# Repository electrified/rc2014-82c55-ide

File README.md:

# 82c55 based IDE interface for the RC2014 computer

## The board
This is a 82c55 based IDE interface for the RC2014 Z80 8-bit computer. IDE uses a 16 bit data bus, so a parallel interface IC is needed to connect one to an 8 bit computer.
This adapter uses the same pin mapping as the ECB Disk IO v3 and the design is heavily based on that. (https://www.retrobrewcomputers.org/lib/exe/fetch.php?media=boards:ecb:diskio-v3:ecb_diskio_v3_-_schematics_-_color_1.0.pdf)

## What can you use this for?

* Connecting an IDE hard drive to your RC2014 and using it in RomWBW, CP/M-IDE or in C programs built with z88dk.

## Features

* 40 pin IDE for normal 3.5" hard drives
* 44 pin IDE header for 2.5" laptop hard drives
* Pins for supplying external 5v for the laptop HD if necessary
* IO port selectable via DIP switch

## Getting started with RomWBW
Wayne Warthen has incorporated support for the RC2014 into [mainline RomWBW](https://github.com/wwarthen/RomWBW). Using this is preferred to Scott Baker's fork as there have been various improvements since Scott forked off. Support for the IDE adapter can be enabled by setting the following in your configuration and rebuilding:

```
PPIDEENABLE     .EQU    TRUE
```

Read the RomWBW readme (`Source/ReadMe.txt`) if you are unfamiliar with the configuration and build process.

The other settings have already been set to the appropriate values in `Source/HBIOS/cfg_rc.asm`, so all is required is to enable PPIDE.

The board I/O address should be set to 0x20; set the A5 switch "on" and all the others off.

## Getting started with z88dk
Support has only recently landed so you'll need a very recent pull of z88dk.
The 82c55 driver, IDE layer and DiskIO are only present within z88dk's RC2014 newlib target. (Not the classic library). 

Phillip Stevens has packaged ChaN's FatFS as a z88dk library, this can be used with above z88dk IDE driver to write programs that can access FAT filesystems.

See https://github.com/feilipu/z88dk-libraries/tree/master/ff and the programs in the example directory.

## CP/M - IDE
Phillip Stevens has made a CP/M version where the CP/M disk images can reside on a FAT filesystem. This requires only a minimal RC2014 setup. See [the GitHub repository](https://github.com/RC2014Z80/RC2014/tree/master/ROMs/CPM-IDE) and [Google groups thread](https://groups.google.com/forum/#!topic/rc2014-z80/V07eugtGFZo) for more details.

## Jumpers and switches
Pin 1 is identified by having square pad.

### SW1
IO address of the board. For operation at 0x20 as RomWBW expects, set the switch marked A5 / 20 to on and all the others to off.

### JP1 - JP4
Described on the back of the board. Some of the pins in the 82c55 C port have a special purpose if you are using the board in mode 2, for something other than being an IDE adapter. Usually the defaults of pins 2-3 are correct.

### JP5
Use external power from J1. Rev 2 of the board only has 2 pins, jumper for bus power.

pins|description
----|------------
1-2 | Bus power
2-3 | External power

## Outputs

* J2 - 40 pin IDE
* J3 - 44 pin IDE

## Bill Of Materials

Reference| Value|Rapid part no|RS part no|Digi-key part no|
---------|------|-------------|----------|----------------|
P1|1x39 right angled pin header|||732-5350-ND|
U1|CS82C55AZ (PLCC version)||921-5567|CS82C55AZ-ND|
U1|PLCC44 socket|22-0350||AE10057-ND|
U3|74HCT04 (DIP)|||296-1605-5-ND|
J2|2x20 shrouded right angled pin header|19-0047||732-5401-ND|
D1|LED of your choosing ;)|||160-1130-ND|
R1|270R through hole resistor (or value suitable for chosen LED)|||CF14JT270RCT-ND|
U2|74HCT688 (DIP)|||296-2131-5-ND|
RN1|10K commoned SIP resistor array (7 resistors, 8 pin)|63-0125||4608X-1-103LF-ND|
C1|0.1uF ceramic capacitor|||BC2665CT-ND|
C2|0.1uF ceramic capacitor|||BC2665CT-ND|
C3|0.1uF ceramic capacitor|||BC2665CT-ND|
J3|2.5" IDE connector 2x22 Shrouded 2mm pitch connector|||WM18567-ND|
SW1|6 switch DIP switch|80-0338||CT2066-ND|
J5|1x02 pin header straight, 2.54mm pitch|||732-5315-ND|
J1|1x02 pin header straight, 2.54mm pitch|||732-5315-ND|
JP1|1x03 pin header straight, 2.54mm pitch|||732-5316-ND|
JP2|1x03 pin header straight, 2.54mm pitch|||732-5316-ND|
JP3|1x03 pin header straight, 2.54mm pitch|||732-5316-ND|
JP4|1x03 pin header straight, 2.54mm pitch|||732-5316-ND|
R3|10K through hole resistor|||CF14JT10K0CT-ND|
R4|10K through hole resistor|||CF14JT10K0CT-ND|
R2|10K through hole resistor|||CF14JT10K0CT-ND|
||Jumpers|||952-2882-ND|

## Construction tips
* Pin 20 of both the 40 pin and 44 pin IDE connector is usually missing as a "key" and is blocked off on many cables. It's best to remove pin 20 from both connectors before soldering them.
* If you're using a 2.5" and powering it from the bus, ensure you have a sufficient power supply. As an example, my 2.5" Seagate Momentum drive is specced to pull up to 2.5A on startup
* If you are using the board as an IDE controller, keep the JP1-4 in their default position of 2-3
* The cutout on the boxed IDE connectors should be towards the RC2014 bus connector in the case of the 44 pin connector, and facing the user in the case of the 40 pin connector.

## Compatibility
The IDE board will not work if the Digital IO v1.0 board is present in your RC2014. This is due to the IO board having very loose addressing - it responds on any IO address below 128 ending with binary 00, 01 or 10. This results in it conflicitng with the IDE adapter.

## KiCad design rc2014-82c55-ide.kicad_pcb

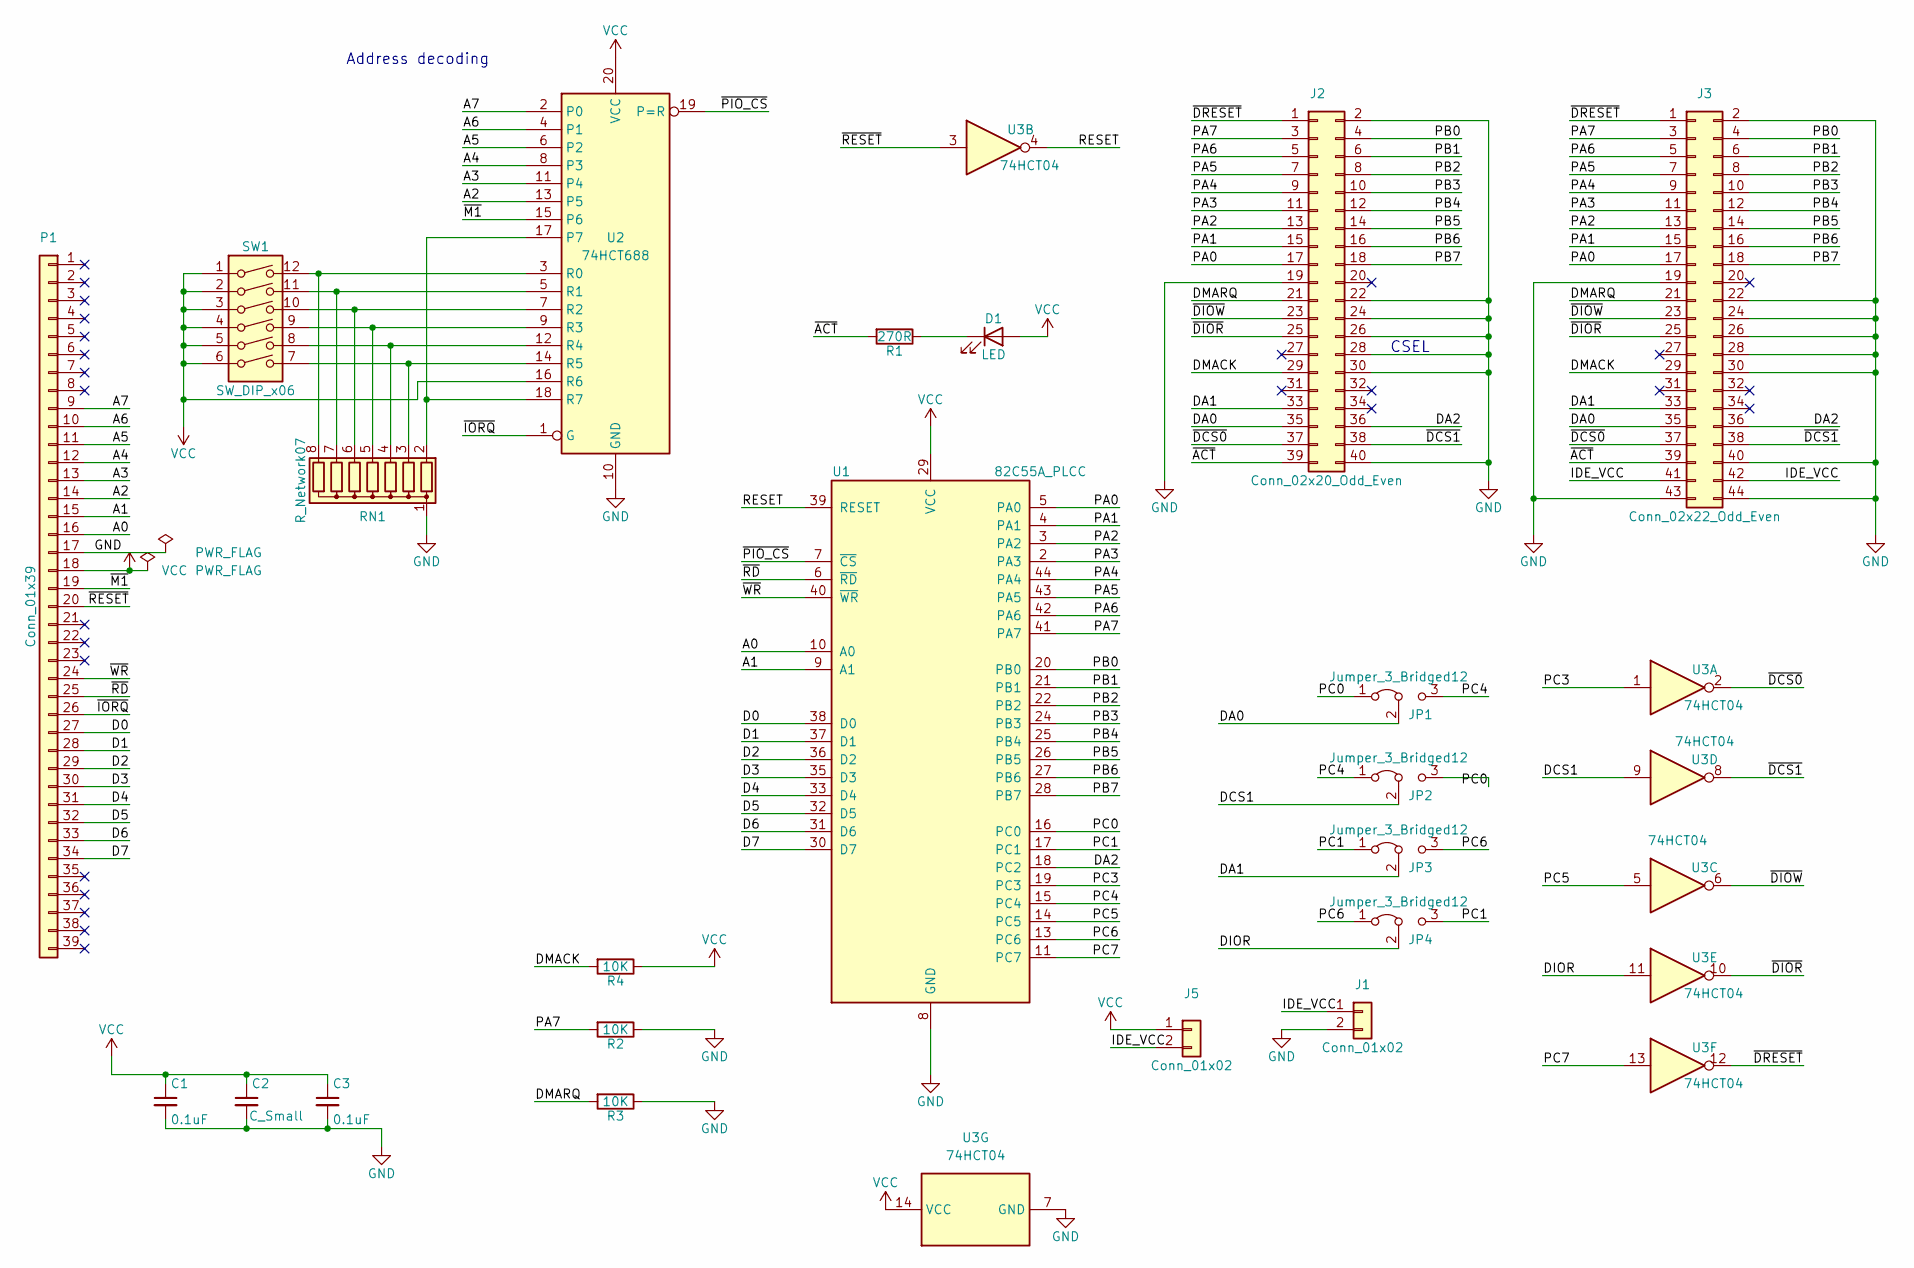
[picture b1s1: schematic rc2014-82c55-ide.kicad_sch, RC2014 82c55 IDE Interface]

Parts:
C1, C3: 0.1uF; C_Disc_D3.0mm_W2.0mm_P2.50mm
C2: C_Small; C_Disc_D3.0mm_W2.0mm_P2.50mm
D1: LED; LED_D3.0mm
J1, J5: Conn_01x02; PinHeader_1x02_P2.54mm_Vertical
J2: Conn_02x20_Odd_Even; PinHeader_2x20_P2.54mm_Vertical
J3: Conn_02x22_Odd_Even; PinHeader_2x22_P2.00mm_Vertical
JP1, JP2, JP3, JP4: Jumper_3_Bridged12; PinHeader_1x03_P2.54mm_Vertical
P1: Conn_01x39; Pin_Header_Straight_1x39_Pitch2.54mm_NoSilk
R1: 270R; R_Axial_DIN0207_L6.3mm_D2.5mm_P7.62mm_Horizontal
R2, R3, R4: 10K; R_Axial_DIN0207_L6.3mm_D2.5mm_P7.62mm_Horizontal
RN1: R_Network07; R_Array_SIP8
SW1: SW_DIP_x06; SW_DIP_SPSTx06_Slide_9.78x17.42mm_W7.62mm_P2.54mm
U1: 82C55A_PLCC; PLCC-44_THT-Socket
U2: 74HCT688; DIP-20_W7.62mm_Socket_LongPads
U3: 74HCT04; DIP-14_W7.62mm_Socket_LongPads

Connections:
/A0: P1.16, U1.10 (A0)
/A1: P1.15, U1.9 (A1)
/A2: P1.14, U2.13 (P5)
/A3: P1.13, U2.11 (P4)
/A4: P1.12, U2.8 (P3)
/A5: P1.11, U2.6 (P2)
/A6: P1.10, U2.4 (P1)
/A7: P1.9, U2.2 (P0)
/D0: P1.27, U1.38 (D0)
/D1: P1.28, U1.37 (D1)
/D2: P1.29, U1.36 (D2)
/D3: P1.30, U1.35 (D3)
/D4: P1.31, U1.33 (D4)
/D5: P1.32, U1.32 (D5)
/D6: P1.33, U1.31 (D6)
/D7: P1.34, U1.30 (D7)
/DA0: J2.35, J3.35, JP1.2 (C)
/DA1: J2.33, J3.33, JP3.2 (C)
/DA2: J2.36, J3.36, U1.18 (PC2)
/DCS1: JP2.2 (C), U3.9
/DIOR: JP4.2 (C), U3.11
/DMACK: J2.29, J3.29, R4.2
/DMARQ: J2.21, J3.21, R3.2
/IDE_VCC: J1.1, J3.41, J3.42, J5.2
/PA0: J2.17, J3.17, U1.5 (PA0)
/PA1: J2.15, J3.15, U1.4 (PA1)
/PA2: J2.13, J3.13, U1.3 (PA2)
/PA3: J2.11, J3.11, U1.2 (PA3)
/PA4: J2.9, J3.9, U1.44 (PA4)
/PA5: J2.7, J3.7, U1.43 (PA5)
/PA6: J2.5, J3.5, U1.42 (PA6)
/PA7: J2.3, J3.3, R2.2, U1.41 (PA7)
/PB0: J2.4, J3.4, U1.20 (PB0)
/PB1: J2.6, J3.6, U1.21 (PB1)
/PB2: J2.8, J3.8, U1.22 (PB2)
/PB3: J2.10, J3.10, U1.24 (PB3)
/PB4: J2.12, J3.12, U1.25 (PB4)
/PB5: J2.14, J3.14, U1.26 (PB5)
/PB6: J2.16, J3.16, U1.27 (PB6)
/PB7: J2.18, J3.18, U1.28 (PB7)
/PC0: JP1.1 (A), JP2.3 (B), U1.16 (PC0)
/PC1: JP3.1 (A), JP4.3 (B), U1.17 (PC1)
/PC3: U1.19 (PC3), U3.1
/PC4: JP1.3 (B), JP2.1 (A), U1.15 (PC4)
/PC5: U1.14 (PC5), U3.5
/PC6: JP3.3 (B), JP4.1 (A), U1.13 (PC6)
/PC7: U1.11 (PC7), U3.13
/RESET: U1.39 (RESET), U3.4
/~ACT: J2.39, J3.39, R1.2
/~DCS0: J2.37, J3.37, U3.2
/~DCS1: J2.38, J3.38, U3.8
/~DIOR: J2.25, J3.25, U3.10
/~DIOW: J2.23, J3.23, U3.6
/~DRESET: J2.1, J3.1, U3.12
/~IORQ: P1.26, U2.1 (G)
/~M1: P1.19, U2.15 (P6)
/~PIO_CS: U1.7 (~CS), U2.19 (P=R)
/~RD: P1.25, U1.6 (~RD)
/~RESET: P1.20, U3.3
/~WR: P1.24, U1.40 (~WR)
GND: C1.2, C2.2, C3.2, J1.2, J2.2, J2.19, J2.22, J2.24, J2.26, J2.28, J2.30, J2.40, J3.2, J3.19, J3.22, J3.24, J3.26, J3.28, J3.30, J3.40, J3.43, J3.44, P1.17, R2.1, R3.1, RN1.1 (common), U1.8 (GND), U2.10 (GND), U3.7 (GND)
unnamed: D1.1 (K), R1.1
unnamed: RN1.2 (R1), U2.17 (P7), U2.18 (R7)
unnamed: RN1.3 (R2), SW1.7, U2.14 (R5)
unnamed: RN1.4 (R3), SW1.8, U2.12 (R4)
unnamed: RN1.5 (R4), SW1.9, U2.9 (R3)
unnamed: RN1.6 (R5), SW1.10, U2.7 (R2)
unnamed: RN1.7 (R6), SW1.11, U2.5 (R1)
unnamed: RN1.8 (R7), SW1.12, U2.3 (R0)
VCC: C1.1, C2.1, C3.1, D1.2 (A), J5.1, P1.18, R4.1, SW1.1, SW1.2, SW1.3, SW1.4, SW1.5, SW1.6, U1.29 (VCC), U2.16 (R6), U2.20 (VCC), U3.14 (VCC)

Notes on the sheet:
CSEL
Address decoding

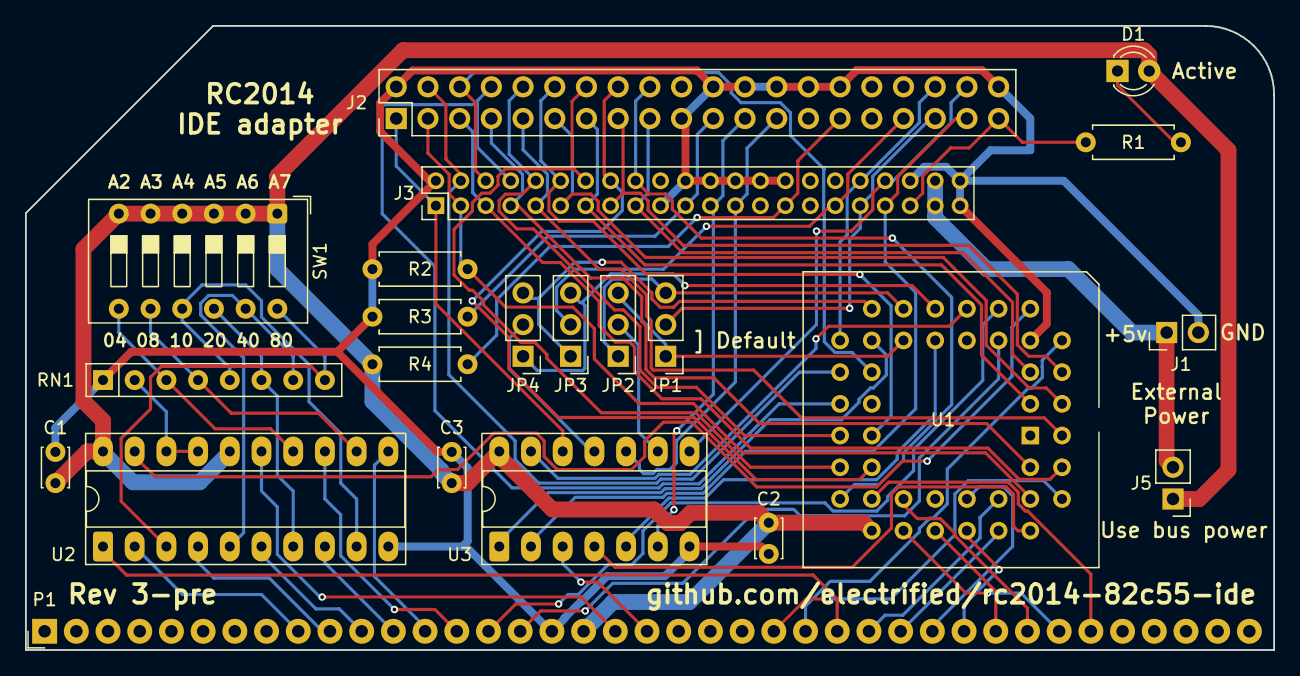
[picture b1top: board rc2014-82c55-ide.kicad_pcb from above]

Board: 2 copper layers, 100.0 x 50.0 mm, 22 parts (0 on the bottom side), 70 nets.

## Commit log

2017-09-18 Relayout
2017-09-22 Add jumpers
2017-09-22 add rtc
2017-09-24 remove clock
2017-09-25 reroute
2017-09-26 R1 as submitted to allpcb
2017-10-01 Update title on pages
2017-10-17 add picture of the board
2017-10-17 a6 -> a5
2017-10-18 r2 as sent for manufacturing
2017-10-24 update readme and board pic
2018-02-05 Update readme with Digi-key part numbers
2022-03-08 Migration to KiCAD 6 WIP
2022-03-08 aisler drc updates
2022-03-09 Don't update to asler DRC rules
2022-03-09 Further kicad 6 migration
2022-03-09 Remove unused footprints
2022-07-25 Regenerate gerbers
2022-10-17 Update PCB components
2025-07-06 update to kicad 9
